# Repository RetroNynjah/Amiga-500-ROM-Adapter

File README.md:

# Amiga 500 ROM Adapter
Adapter board that allows use of regular EPROMS on Amiga 500 Rev 5 boards
A500 boards with revision 6 and higher don't have these problems and don't need this adapter.

<br/>

To be able to use regular 27C400 or 27C800 EPROMS on Amiga 500 Rev 5 boards, you will need to lift out pin 31 on the chip, connecting it to VCC and instead connect pin 31 in the socket to pin 1 on the chip.
If that wasn't enough there are compatibility problems between some EPROMS and some machines/CPUs which requires pull-up resistors on the address pins.
This simple adapter board solves both problems. It re-routes the EPROM pins and has place for two optional resistor nets.

<br/>
*Diag ROM installed on a Rev 5 board*

## BOM
 |Component|Pcs |Name|Comment|
 |:--------|---:|:---|:------|
 | 100nF  ceramic capacitor| 1 | C1 | |
 | 4.7k resistor array | 1 | RN1, RN2 | 9 resistor arry (10SIP). 10k is probably OK as well| 
 | DIL-40 socket | 1 || EPROM socket for top side| 
 | 20-pin header | 2 || Round machined pin headers for bottom side (mates with motherboard) | 

Retro Ninja

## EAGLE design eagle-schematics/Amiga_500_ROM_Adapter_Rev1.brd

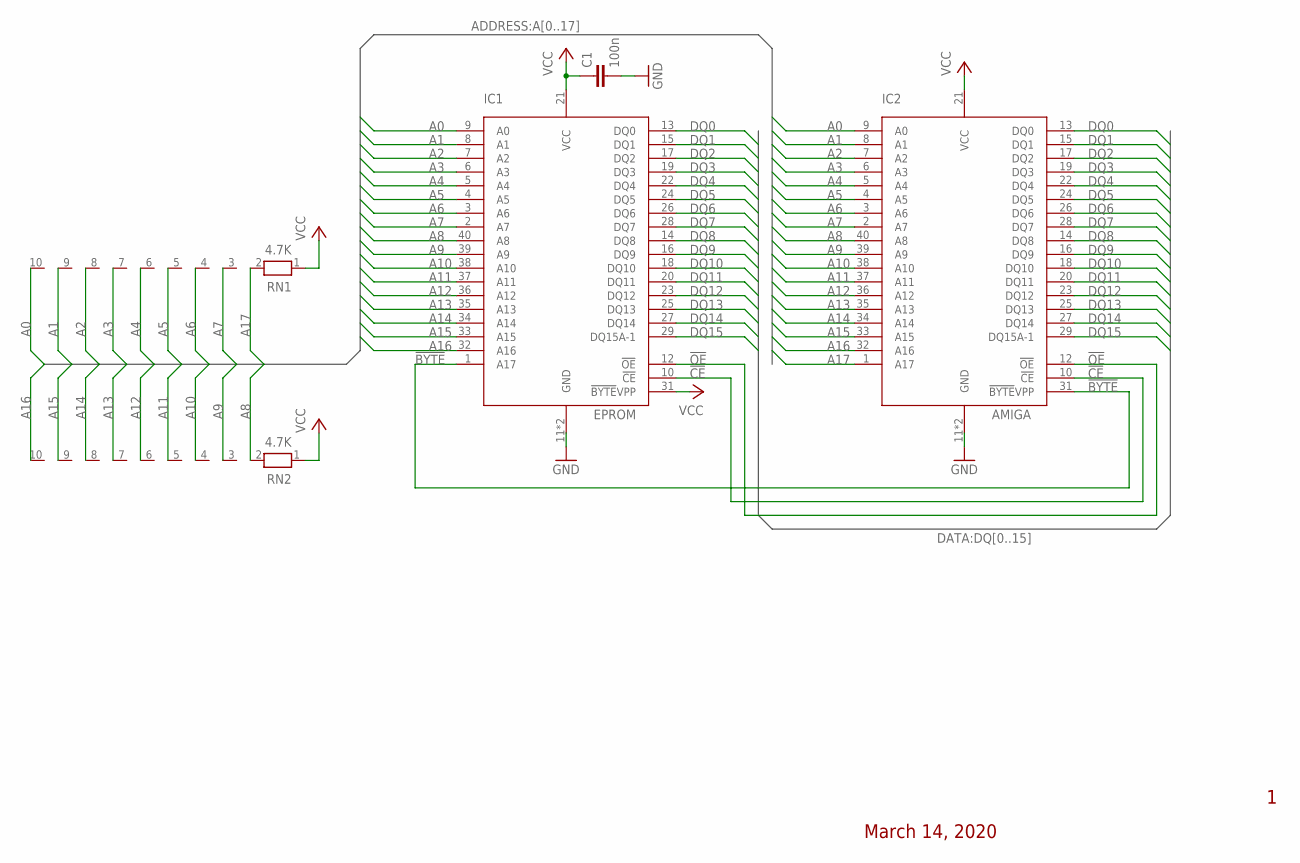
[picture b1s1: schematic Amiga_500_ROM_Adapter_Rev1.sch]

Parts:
C1: 100n; C025-025X050
IC1: EPROM; DIL40-6
IC2: AMIGA; DIL40-6
RN1, RN2: 4.7K; RN-10

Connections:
!BYTE: IC1.1 (A17), IC2.31 (!BYTE!VPP)
!CE: IC1.10 (!CE), IC2.10 (!CE)
!OE: IC1.12 (!OE), IC2.12 (!OE)
A0: IC1.9 (A0), IC2.9 (A0), RN1.10
A1: IC1.8 (A1), IC2.8 (A1), RN1.9
A2: IC1.7 (A2), IC2.7 (A2), RN1.8
A3: IC1.6 (A3), IC2.6 (A3), RN1.7
A4: IC1.5 (A4), IC2.5 (A4), RN1.6
A5: IC1.4 (A5), IC2.4 (A5), RN1.5
A6: IC1.3 (A6), IC2.3 (A6), RN1.4
A7: IC1.2 (A7), IC2.2 (A7), RN1.3
A8: IC1.40 (A8), IC2.40 (A8), RN2.2
A9: IC1.39 (A9), IC2.39 (A9), RN2.3
A10: IC1.38 (A10), IC2.38 (A10), RN2.4
A11: IC1.37 (A11), IC2.37 (A11), RN2.5
A12: IC1.36 (A12), IC2.36 (A12), RN2.6
A13: IC1.35 (A13), IC2.35 (A13), RN2.7
A14: IC1.34 (A14), IC2.34 (A14), RN2.8
A15: IC1.33 (A15), IC2.33 (A15), RN2.9
A16: IC1.32 (A16), IC2.32 (A16), RN2.10
A17: IC2.1 (A17), RN1.2
DQ0: IC1.13 (DQ0), IC2.13 (DQ0)
DQ1: IC1.15 (DQ1), IC2.15 (DQ1)
DQ2: IC1.17 (DQ2), IC2.17 (DQ2)
DQ3: IC1.19 (DQ3), IC2.19 (DQ3)
DQ4: IC1.22 (DQ4), IC2.22 (DQ4)
DQ5: IC1.24 (DQ5), IC2.24 (DQ5)
DQ6: IC1.26 (DQ6), IC2.26 (DQ6)
DQ7: IC1.28 (DQ7), IC2.28 (DQ7)
DQ8: IC1.14 (DQ8), IC2.14 (DQ8)
DQ9: IC1.16 (DQ9), IC2.16 (DQ9)
DQ10: IC1.18 (DQ10), IC2.18 (DQ10)
DQ11: IC1.20 (DQ11), IC2.20 (DQ11)
DQ12: IC1.23 (DQ12), IC2.23 (DQ12)
DQ13: IC1.25 (DQ13), IC2.25 (DQ13)
DQ14: IC1.27 (DQ14), IC2.27 (DQ14)
DQ15: IC1.29 (DQ15A-1), IC2.29 (DQ15A-1)
GND: C1.2, IC1.11 (GND), IC1.30 (GND), IC2.11 (GND), IC2.30 (GND)
VCC: C1.1, IC1.21 (VCC), IC1.31 (!BYTE!VPP), IC2.21 (VCC), RN1.1, RN2.1

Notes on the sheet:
March 14, 2020

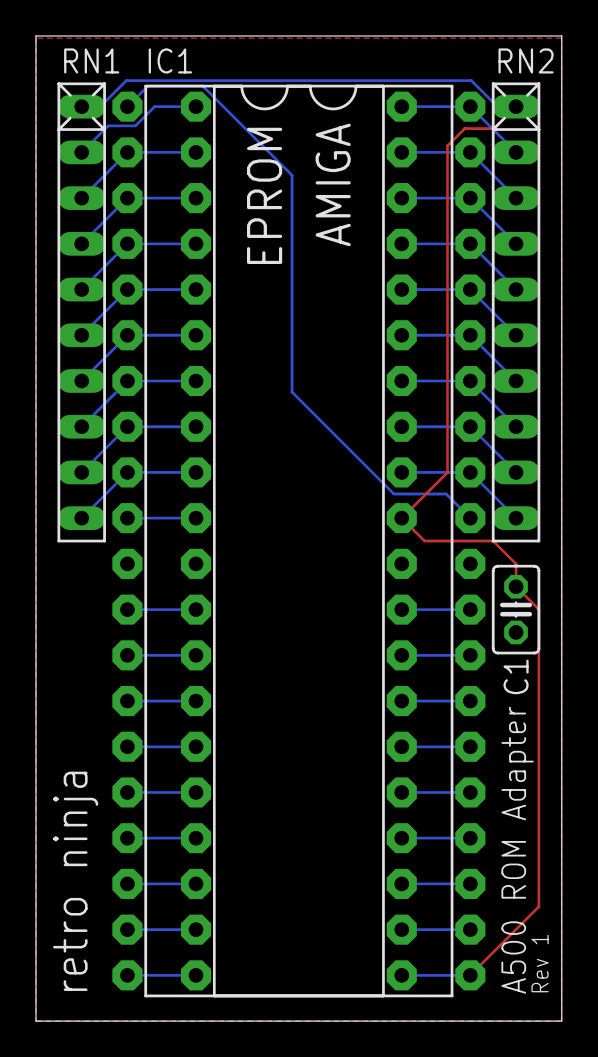
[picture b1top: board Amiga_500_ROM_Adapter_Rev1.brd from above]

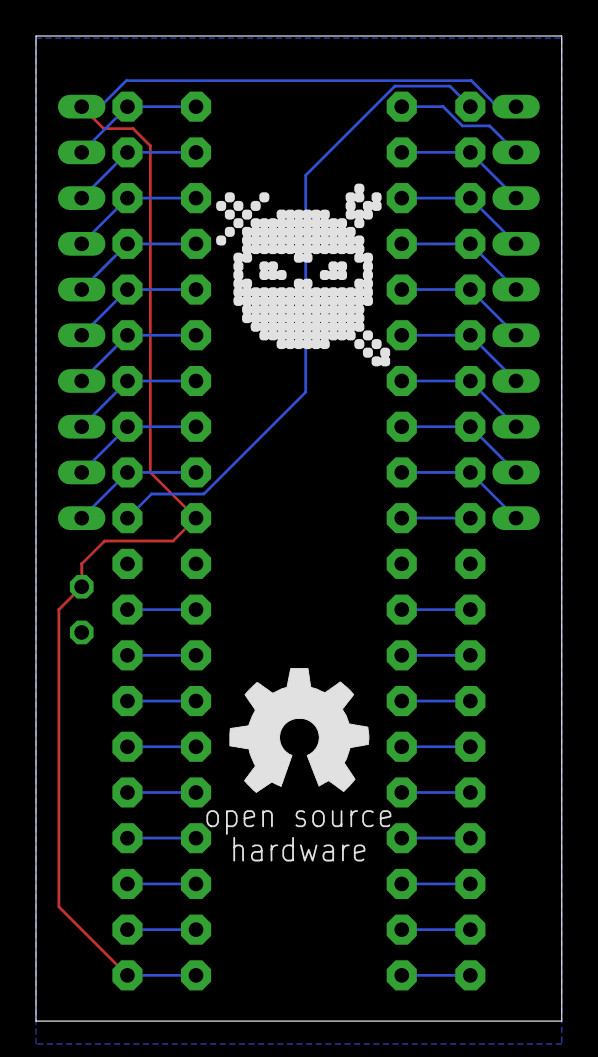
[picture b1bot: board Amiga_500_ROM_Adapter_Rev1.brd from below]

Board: 2 copper layers, 29.2 x 54.7 mm, 7 parts (2 on the bottom side), 39 nets.

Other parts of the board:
E$1: OSHW_8MM
U$1: RETRONINJA_NOTEXT_10MM

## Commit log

2020-07-15 First version
2020-08-01 Create LICENSE
